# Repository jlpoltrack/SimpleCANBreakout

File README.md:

# SimpleCANBreakout

A small (31.5 × 15.5 mm) CAN transceiver breakout. It converts a microcontroller's logic-level CAN TX/RX to a CAN bus, with an onboard 3.3 V regulator and 120 Ω termination. All connections are large solder pads, so wires can be soldered directly to the board.

Designed in KiCad 10. See [SimpleCANBreakoutMicro](https://github.com/jlpoltrack/SimpleCANBreakoutMicro) for a smaller version with a JST-GH connector, an XC6206 regulator, and switchable termination.

## Features

- SN65HVD230 3.3 V CAN transceiver, wired for high-speed mode (up to 1 Mbps)
- AMS1117 3.3 V LDO, so the board runs from a single 5 V supply
- 120 Ω termination resistor, always fitted
- 2-layer, 1.6 mm PCB, parts on the top side only
- All parts are JLCPCB basic parts, except U1 (preferred extended)

## Connections

All pads are 2.5 × 2.5 mm, labelled on the silkscreen.

**MCU side** (right column, top to bottom)

| Pad | Silk | Signal |
|-----|------|--------|
| TP8 | R    | CAN RX |
| TP7 | T    | CAN TX |
| TP5 | 5    | +5V    |
| TP6 | G    | GND    |

**CAN bus side** (left column, top to bottom)

| Pad | Silk | Signal |
|-----|------|--------|
| TP3 | 5    | +5V    |
| TP1 | H    | CANH   |
| TP2 | L    | CANL   |
| TP4 | G    | GND    |

The +5V pads on both sides are connected, so the board can be powered from either side. CAN TX/RX are 3.3 V logic.

## Termination

R1 (120 Ω) is permanently connected across CANH/CANL, so the board is meant to sit at an end of the bus. Leave R1 unpopulated if the board is used mid-bus.

## Bill of materials

| Ref        | Value       | Package  | LCSC   |
|------------|-------------|----------|--------|
| U1         | SN65HVD230  | SOIC-8   | C12084 |
| U2         | AMS1117-3.3 | SOT-223  | C6186  |
| C1, C4, C6 | 10 µF       | 0603     | C19702 |
| C2, C3, C5 | 100 nF      | 0603     | C14663 |
| R1         | 120 Ω       | 0603     | C22787 |

## Files

- `SimpleCANBreakout.kicad_sch` / `.kicad_pcb` / `.kicad_pro` — KiCad project
- `SimpleCANBreakout.pdf` — schematic
- `production/` — fabrication outputs generated with the [Fabrication Toolkit](https://github.com/bennymeg/Fabrication-Toolkit) plugin: Gerbers and drill files (`SimpleCANBreakout.zip`), BOM, and pick-and-place positions, ready for JLCPCB

## License

[MIT](LICENSE)

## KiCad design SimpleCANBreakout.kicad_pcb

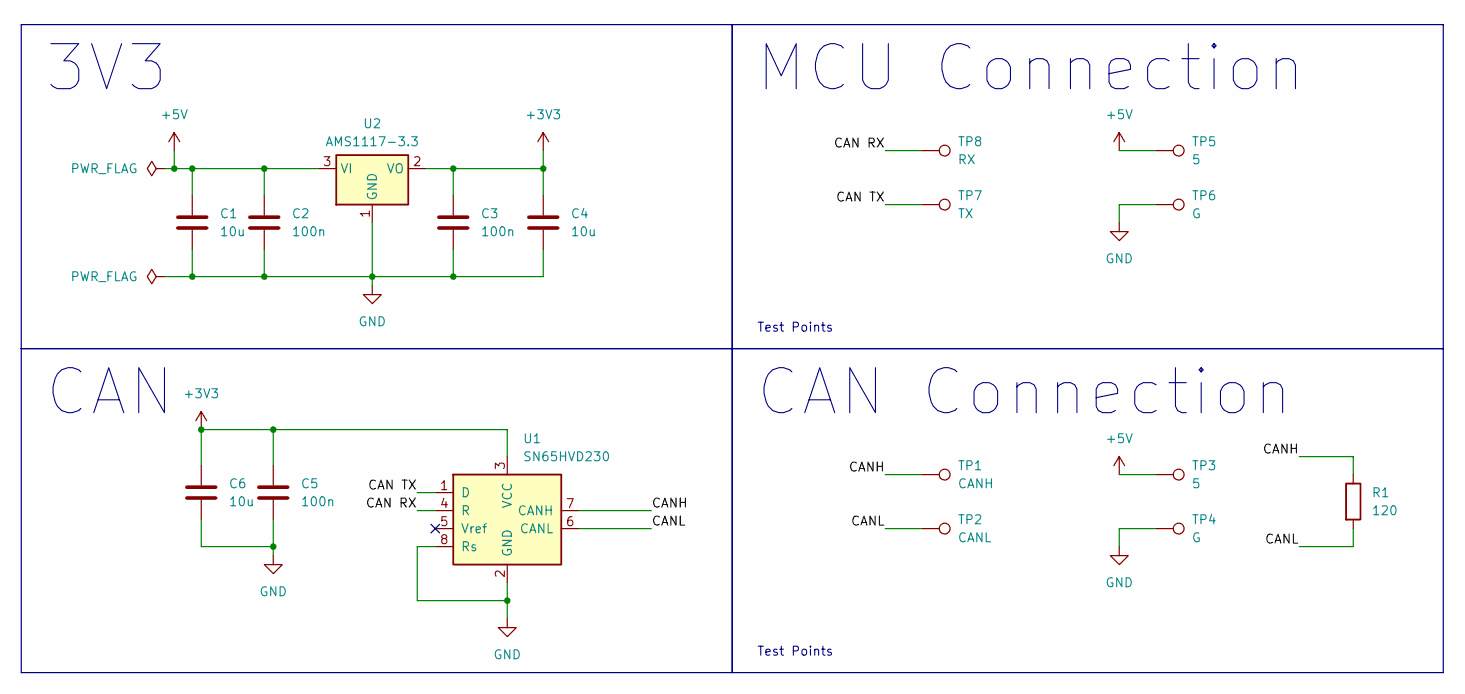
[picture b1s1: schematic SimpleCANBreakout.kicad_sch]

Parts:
C1, C4, C6: 10u; C_0603_1608Metric_Pad1.08x0.95mm_HandSolder; LCSC Part C19702
C2, C3, C5: 100n; C_0603_1608Metric_Pad1.08x0.95mm_HandSolder; LCSC Part C14663
R1: 120; R_0603_1608Metric_Pad0.98x0.95mm_HandSolder; LCSC Part C22787
TP1: CANH; TestPoint_Pad_2.5x2.5mm
TP2: CANL; TestPoint_Pad_2.5x2.5mm
TP3, TP5: 5; TestPoint_Pad_2.5x2.5mm
TP4, TP6: G; TestPoint_Pad_2.5x2.5mm
TP7: TX; TestPoint_Pad_2.5x2.5mm
TP8: RX; TestPoint_Pad_2.5x2.5mm
U1: SN65HVD230; SOIC-8_3.9x4.9mm_P1.27mm; LCSC Part C12084
U2: AMS1117-3.3; SOT-223-3_TabPin2; LCSC Part C6186

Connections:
+3V3: C3.1, C4.1, C5.1, C6.1, U1.3 (VCC), U2.2 (VO)
+5V: C1.1, C2.1, TP3.1 (1_1), TP5.1 (1_1), U2.3 (VI)
/CAN RX: TP8.1 (1_1), U1.4 (R)
/CAN TX: TP7.1 (1_1), U1.1 (D)
/CANH: R1.1, TP1.1 (1_1), U1.7 (CANH)
/CANL: R1.2, TP2.1 (1_1), U1.6 (CANL)
GND: C1.2, C2.2, C3.2, C4.2, C5.2, C6.2, TP4.1 (1_1), TP6.1 (1_1), U1.2 (GND), U1.8 (Rs), U2.1 (GND)

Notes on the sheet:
3V3
MCU Connection
CAN
CAN Connection
Test Points

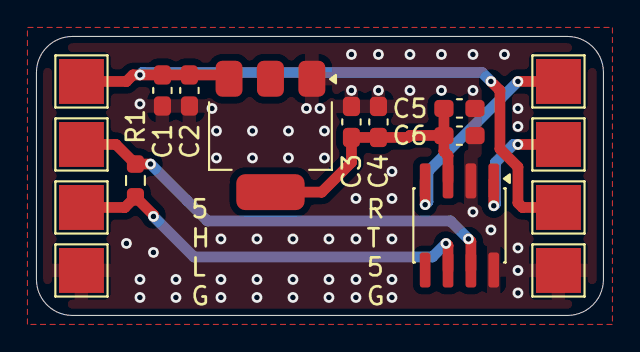
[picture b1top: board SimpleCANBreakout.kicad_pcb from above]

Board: 2 copper layers, 31.5 x 15.5 mm, 17 parts (0 on the bottom side), 7 nets.

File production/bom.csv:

Designator,Footprint,Quantity,Value,LCSC Part #
"C1, C4, C6",0603,3,10u,C19702
"C2, C3, C5",0603,3,100n,C14663
R1,0603,1,120,C22787
TP1,TestPoint_Pad_2.5x2.5mm,1,CANH,
TP2,TestPoint_Pad_2.5x2.5mm,1,CANL,
"TP3, TP5",TestPoint_Pad_2.5x2.5mm,2,5,
"TP4, TP6",TestPoint_Pad_2.5x2.5mm,2,G,
TP7,TestPoint_Pad_2.5x2.5mm,1,TX,
TP8,TestPoint_Pad_2.5x2.5mm,1,RX,
U1,SOIC-8_3.9x4.9mm_P1.27mm,1,SN65HVD230,C12084
U2,SOT-223-3_TabPin2,1,AMS1117-3.3,C6186
